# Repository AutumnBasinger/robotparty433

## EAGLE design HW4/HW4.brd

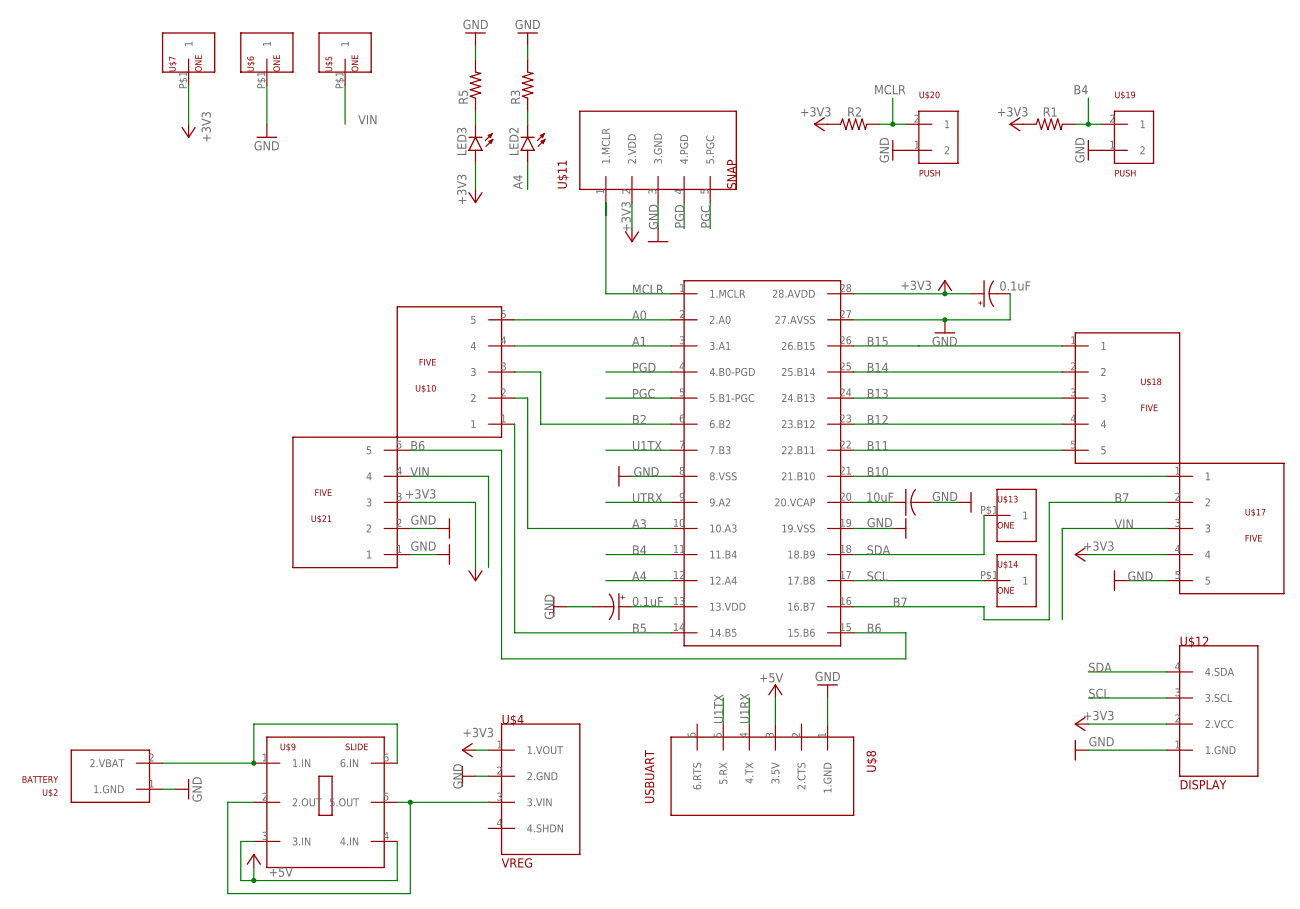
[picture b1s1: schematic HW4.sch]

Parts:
C1: 10uF; C025-030X050
C2, C3: 0.1uF; B45181B
LED2, LED3: LED3MM
R1, R2, R3, R5: R-US_0207/7; 0207/7
U$1: PIC32MX170F256B; DIL28-3
U$2: BATTERY
U$4: VREG
U$5, U$6, U$7, U$13, U$14: ONE
U$8: USBUART
U$9: SLIDE
U$10, U$17, U$18, U$21: FIVE
U$11: SNAP
U$12: DISPLAY
U$19, U$20: PUSH

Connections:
+3V3: C3.+, LED3.A, R1.1, R2.1, U$1.28 (28.AVDD), U$4.1 (1.VOUT), U$7.P$1, U$11.2 (2.VDD), U$12.2 (2.VCC), U$17.4, U$21.3
+5V: U$8.3 (3.5V), U$9.3 (3.IN), U$9.4 (4.IN)
A0: U$1.2 (2.A0), U$10.5
A1: U$1.3 (3.A1), U$10.4
A3: U$1.10 (10.A3), U$10.2
A4: LED2.A, U$1.12 (12.A4)
B2: U$1.6 (6.B2), U$10.3
B4: R1.2, U$1.11 (11.B4), U$19.2 (1)
B5: U$1.14 (14.B5), U$10.1
B6: U$1.15 (15.B6), U$21.5
B7: U$1.16 (16.B7), U$17.2
B10: U$1.21 (21.B10), U$17.1
B11: U$1.22 (22.B11), U$18.5
B12: U$1.23 (23.B12), U$18.4
B13: U$1.24 (24.B13), U$18.3
B14: U$1.25 (25.B14), U$18.2
B15: U$1.26 (26.B15), U$18.1
GND: C1.2, C2.-, C3.-, R3.2, R5.2, U$1.8 (8.VSS), U$1.19 (19.VSS), U$1.27 (27.AVSS), U$2.1 (1.GND), U$4.2 (2.GND), U$6.P$1, U$8.1 (1.GND), U$11.3 (3.GND), U$12.1 (1.GND), U$17.5, U$19.1 (2), U$20.1 (2), U$21.1, U$21.2
MCLR: R2.2, U$1.1 (1.MCLR), U$11.1 (1.MCLR), U$20.2 (1)
unnamed: C2.+, U$1.13 (13.VDD)
unnamed: LED3.K (C), R5.1
unnamed: C1.1, U$1.20 (20.VCAP)
unnamed: LED2.K (C), R3.1
unnamed: U$2.2 (2.VBAT), U$9.1 (1.IN), U$9.6 (6.IN)
unnamed: U$4.3 (3.VIN), U$9.2 (2.OUT), U$9.5 (5.OUT)
PGC: U$1.5 (5.B1-PGC), U$11.5 (5.PGC)
PGD: U$1.4 (4.B0-PGD), U$11.4 (4.PGD)
SCL: U$1.17 (17.B8), U$12.3 (3.SCL), U$14.P$1
SDA: U$1.18 (18.B9), U$12.4 (4.SDA), U$13.P$1
U1RX: U$8.4 (4.TX)
U1TX: U$1.7 (7.B3), U$8.5 (5.RX)
UTRX: U$1.9 (9.A2)
VIN: U$5.P$1, U$17.3, U$21.4

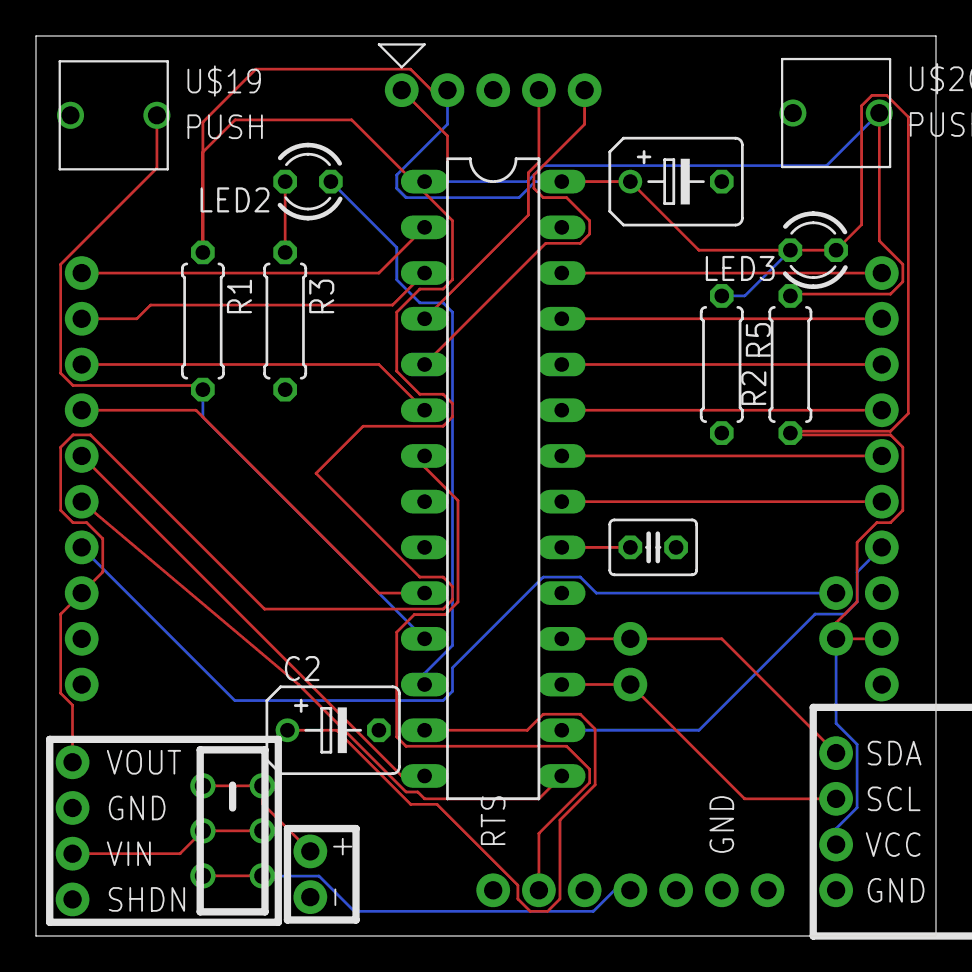
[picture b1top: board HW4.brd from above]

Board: 2 copper layers, 50.0 x 50.0 mm, 27 parts (0 on the bottom side), 31 nets.

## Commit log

2022-04-03 Edit #pragma configs
2022-04-04 Add TRIS, LAT, attempt while (fail)
2022-04-04 Update while (works)
2022-04-05 Initial video code (build success)
2022-04-05 Blink + message on button press (works)
2022-04-10 Eagle library first pass
2022-04-10 Schematic first past
2022-04-13 Finish library + schematic
2022-04-14 Board attempt, awful
2022-04-15 Sample code first pass
2022-04-19 hw5 progress
2022-04-19 hw5 (works)
2022-04-19 hw5 add voltage pic
2022-04-20 hw6 first pass
2022-04-20 hw6 (works)
2022-04-20 hw4 board/schematic update (finish)
2022-04-27 hw7 (raw data shows)
2022-04-27 hw7 (plot average)
2022-04-27 hw7 (add plot pics)
2022-04-28 hw9 (LEDs rainbow)
2022-04-30 hw8 (builds, doesn't flash)
2022-05-05 hw8 (screen works)
2022-05-07 hw8 (prints hz)
2022-05-11 hw10 (confused)
2022-05-11 hw10 (works)
2022-06-08 hw11 (cam selfie) + hw12 (robot photos)
